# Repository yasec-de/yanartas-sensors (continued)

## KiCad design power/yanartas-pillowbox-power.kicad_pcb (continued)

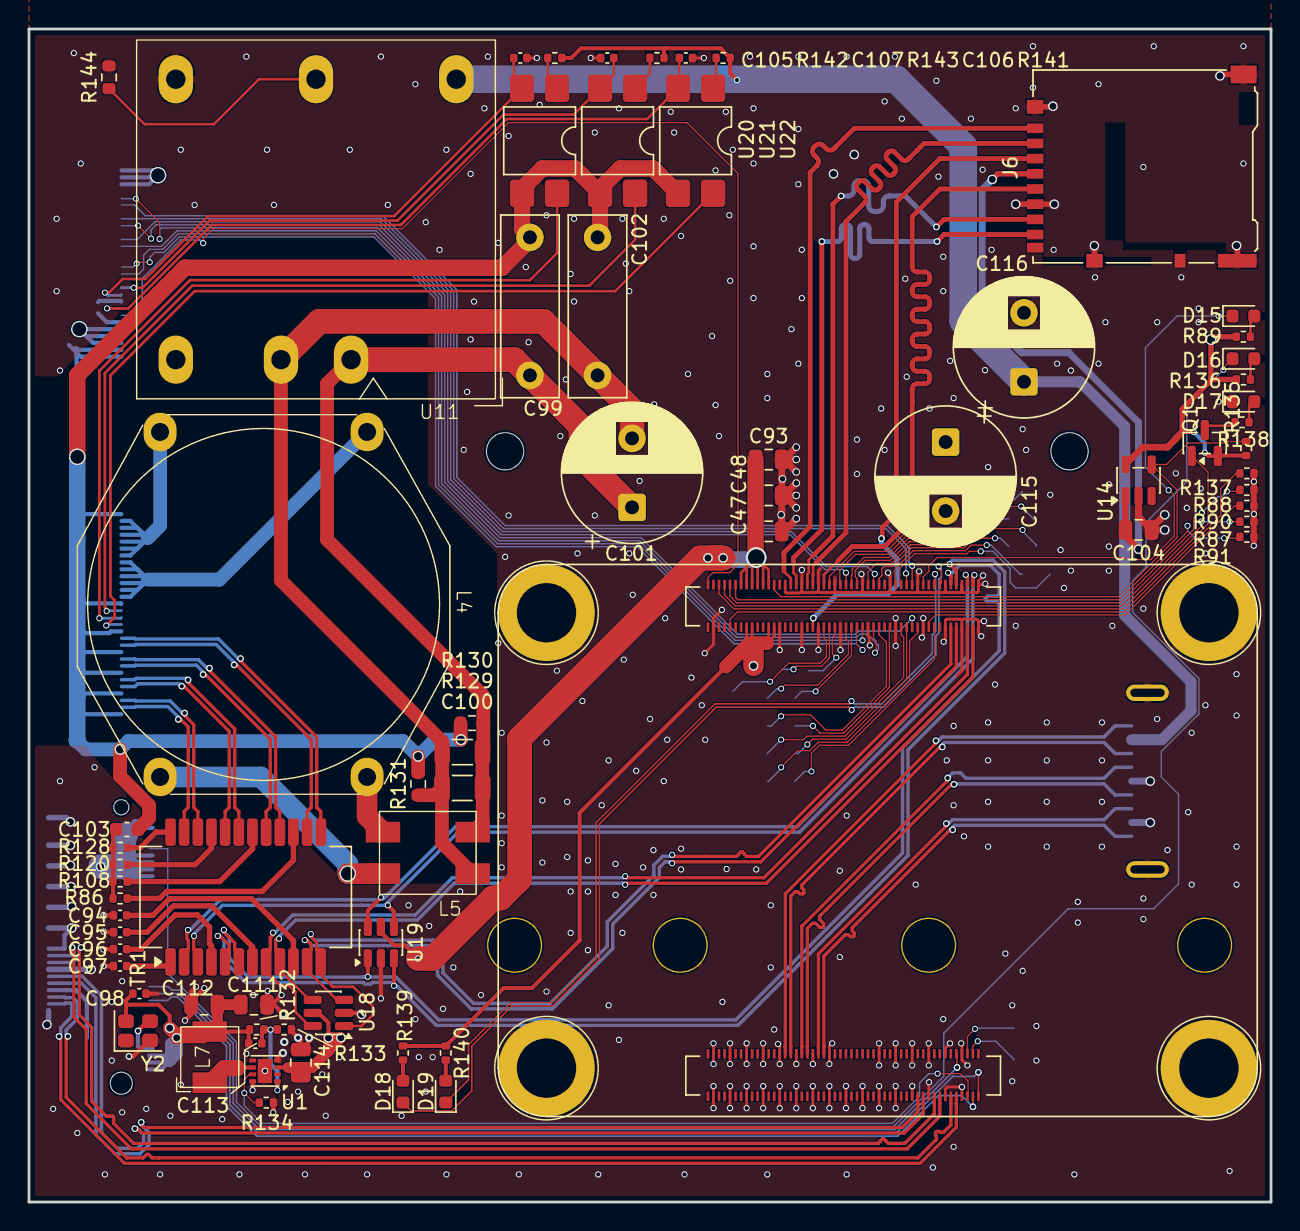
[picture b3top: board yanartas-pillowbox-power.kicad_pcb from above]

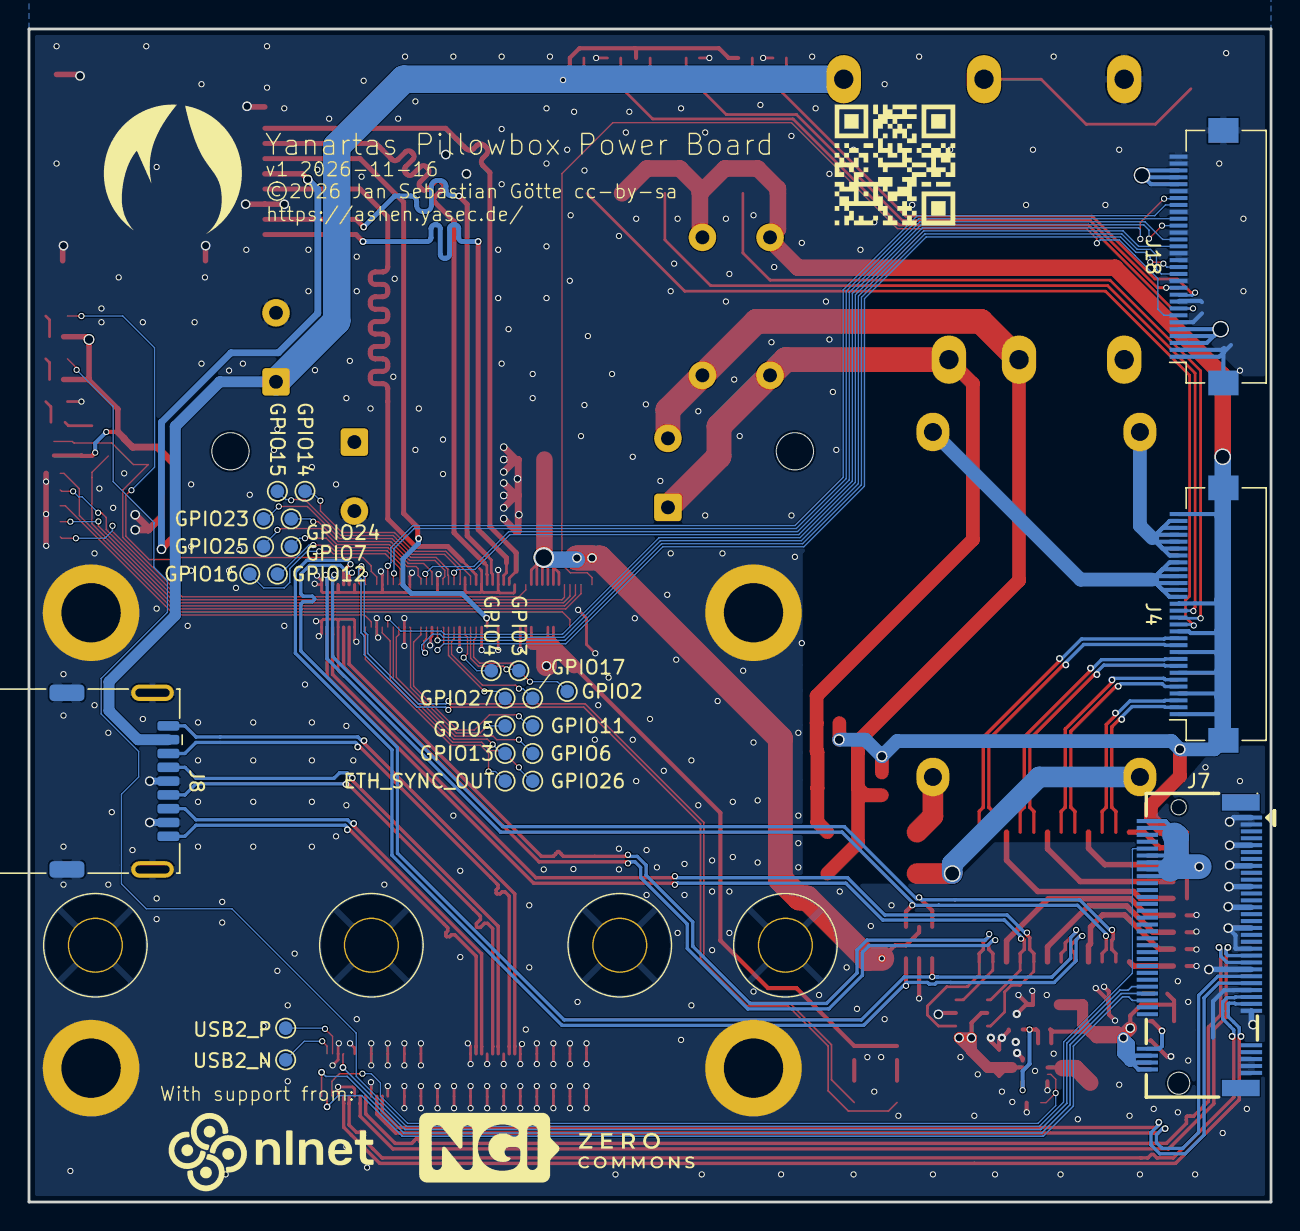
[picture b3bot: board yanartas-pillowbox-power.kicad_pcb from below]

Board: 4 copper layers, 90.0 x 85.0 mm, 109 parts (33 on the bottom side), 119 nets.

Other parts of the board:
ashen-logo_w10.00mm: G*****; ashen-logo_w10.00mm
kobee-studio-6AF9AA16: Kobee Studio; kobee-studio-6AF9AA16
ngi-zero-commons-logo_w20.00mm: G*****; ngi-zero-commons-logo_w20.00mm
nlnet-logo_w15.00mm: G*****; nlnet-logo_w15.00mm
